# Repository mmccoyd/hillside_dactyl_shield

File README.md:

# Hillside Dactyl Shield

|                 |                 |
|:-----------     |:----------------|
|  |  |

These shields link the parts of a small Dactyl keyboard:
    the MCU, key matrix, battery, USB-C split, display, and underglow.
The shield fits below the index columns and display area of a
    choc Dactyl keyboard.
They should be useful for creating any modest sized Dactyl,
    but were designed for the
    [Hillside Dactyl 50](https://github.com/mmccoyd/hillside_dactyl_50).

## Feature levels

There are three main choice points in a shield cost vs features trade off.
See the wiki ordering page for costs.

- Wireless with key matrix, display, reset, power switch, and battery.
- Wired with ESD protection and PCBA parts placement.
- Vic link, LED underglow, and a decently clean emissions profile,
  using a four layer board with higher setup fees.

## What the shield provides

- A header to socket or solder a ProMicro footprint MCU.
- Key matrix headers for four or five rows, six columns,
   five thumbs, and three external switches.
- A battery switch and JST connector.
- A display header and Vik connector.
- Underglow or side indicator LEDs with power switch and cutoff solder jumpers.
- Extensive ESD protection on the USB-C split connection.
- Four or two layer construction options and PCBA construction.

## Designed as a four layer board, but also to work with two layers

Our highest priority was a cleanly working key matrix,
 followed by an informational display or LED.
Both with clean signal integrity and a properly low
  spurious emissions profile.
So the key matrix routing came first,
  followed by SPI routing for the display and LEDs.
Best practice for SPI seemed to be a four layer board,
    as SPI has fast edge transitions on typical keyboard processors.
Best practice is also to route high speed signals like SPI first,
    but I care more about the key matrix,
    and it seems to have high speed signal edge transitions as well.
So our layout is based on four layers with the inner layers as ground.
That gives the best signal integrity
  and hopefully a properly low emissions profile.
(The signal integrity in the wires flapping around inside the case
    is a different question.)

But four layer boards are more expensive in the small batches
    common with hobbyists.
So a two layer fabrication is also possible,
    as the MCU has direct outer layer ground traces to all ground pin uses.
But with two layers,
  the signal integrity for the matrix, LED, and display is unknown
  and an improper spurious emissions profile seems likely.

## Ordering board fabrication, parts, and building

[Releases](https://github.com/mmccoyd/hillside_dactyl_shield/releases)
    has the files for fabrication.

The [wiki](https://github.com/mmccoyd/hillside_dactyl_shield/wiki)
  has information on parts and ordering.
An example of its use in a keyboard can be found in the
    [Hillside Dactyl 50](https://github.com/mmccoyd/hillside_dactyl_50).

## Firmware

The [Hillside Dactyl 50](https://github.com/mmccoyd/hillside_dactyl_50),
    keyboard's ZMK and QMK firmware
    should be good starting points for creating similar Dactyls.

## Design notes

- The MCU goes face down.
  A dactyl is often not one's first ergo board
  and most ergo boards with a socketed MCU have it face down,
  so most of those building a dactyl likely have MCUs already pinned that way.
- The PCBA is configured for the Vik connector and battery and LED switches.
  It uses KiBot and is being tested using JLC's Economic PCBA.

## Other controller boards

Some other shields provide related abilities, including:

- A board with a built-in processor is
[BastardKB](https://bastardkb.com/)'s [Splinktegrated](https://bastardkb.com/product/splinktegrated-rp2040-controller/)
- The [Keebio Stampy](https://keeb.io/products/stampy-prototypes-rp2040-usb-c-controller-board-for-handwiring)
   RP2040 has three integrated switch footprints plus 26 pin breakouts.

## Images

There is also a STEP file in the GitHub action result files.

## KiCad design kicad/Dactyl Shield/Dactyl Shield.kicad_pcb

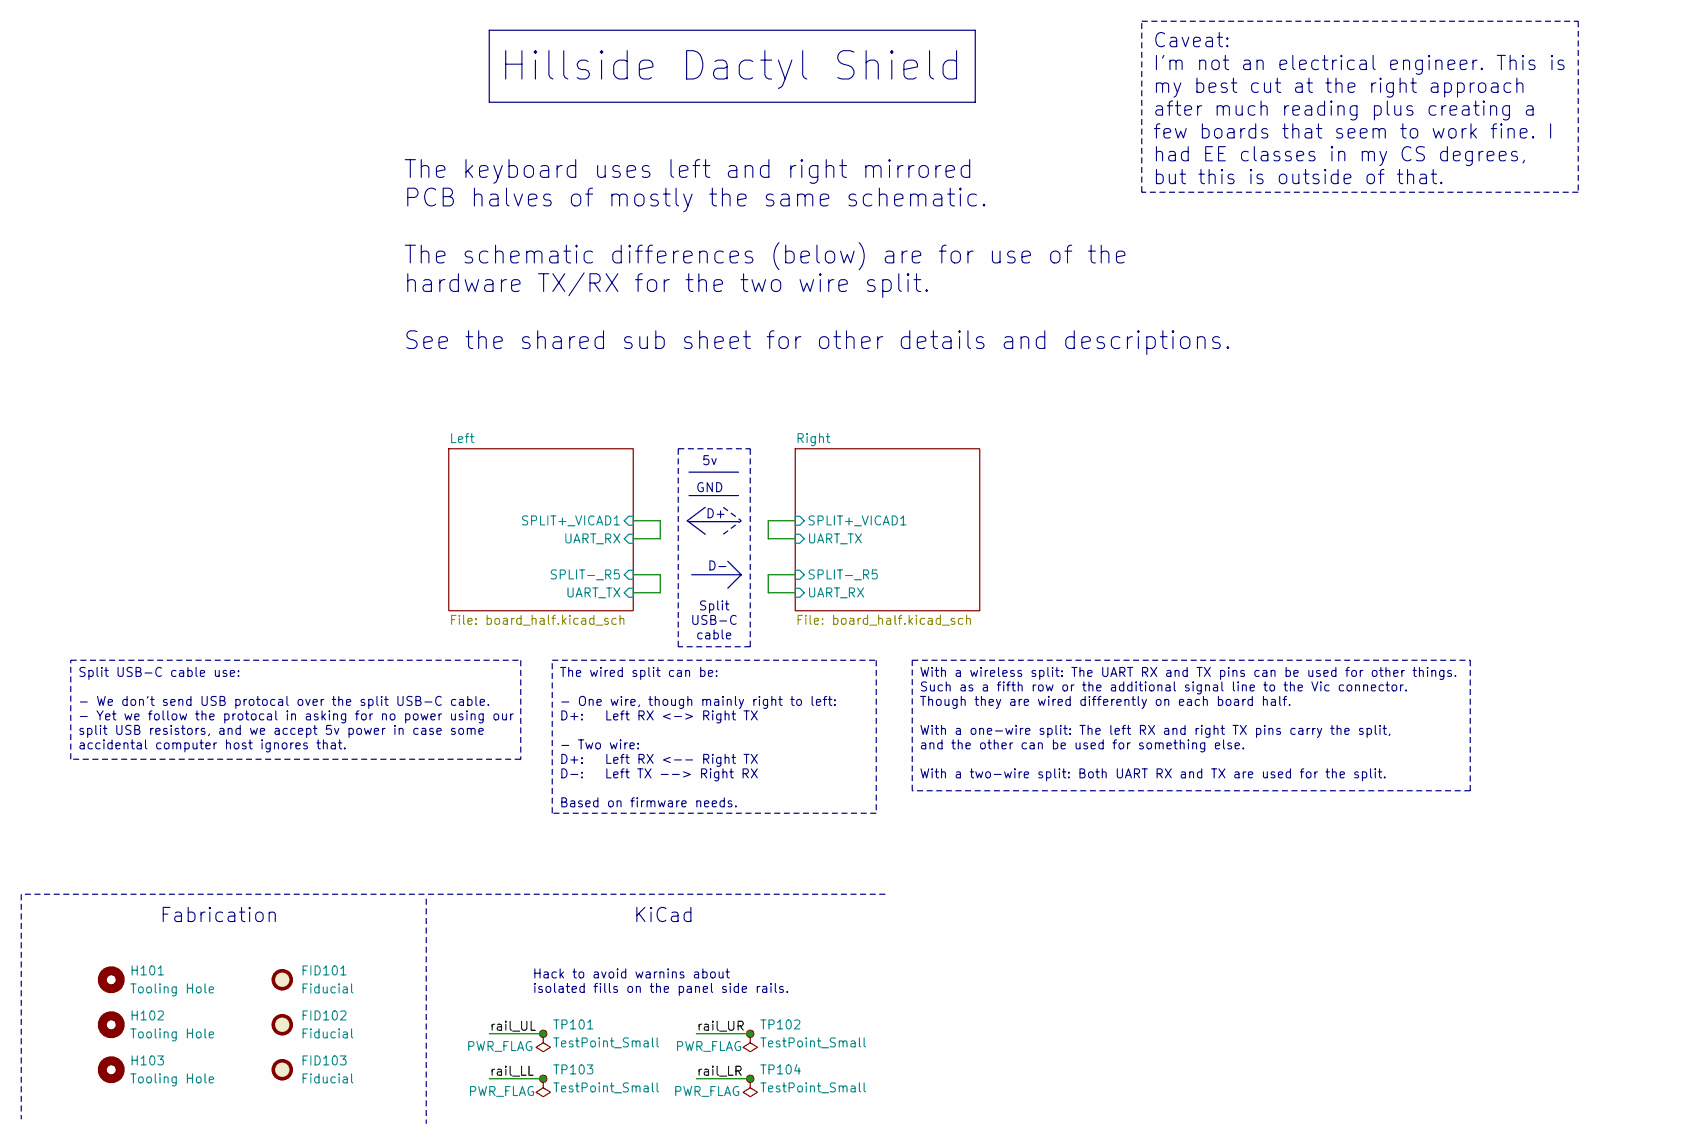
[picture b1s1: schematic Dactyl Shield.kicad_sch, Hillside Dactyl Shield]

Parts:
FID101, FID102, FID103: Fiducial; Fiducial_1mm_Mask2mm
H101, H102, H103: Tooling Hole; ToolingHole_1.152mm
TP101, TP102, TP103, TP104: TestPoint_Small; TestPoint_THTPad_D1.0mm_Drill0.5mm

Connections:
/rail_LL: TP103.1
/rail_LR: TP104.1
/rail_UL: TP101.1
/rail_UR: TP102.1

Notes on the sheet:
KiCad
Fabrication
${TITLE}
GND
The keyboard uses left and right mirrored PCB halves of mostly the same schematic. The schematic differences (below) are for use of the hardware TX/RX for the two wire split. See the shared sub sheet for other details and descriptions.
Hack to avoid warnins about isolated fills on the panel side rails.
Split USB-C cable use: - We don't send USB protocal over the split USB-C cable. - Yet we follow the protocal in asking for no power using our split USB resistors, and we accept 5v power in case some accidental computer host ignores that.
Caveat: I'm not an electrical engineer. This is my best cut at the right approach after much reading plus creating a few boards that seem to work fine. I had EE classes in my CS degrees, but this is outside of that.
With a wireless split: The UART RX and TX pins can be used for other things. Such as a fifth row or the additional signal line to the Vic connector. Though they are wired differently on each board half. With a one-wire split: The left RX and right TX pins carry the split, and the other can be used 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
The wired split can be: - One wire, though mainly right to left: D+: Left RX <-> Right TX - Two wire: D+: Left RX <-- Right TX D-: Left TX --> Right RX Based on firmware needs.
Split USB-C cable

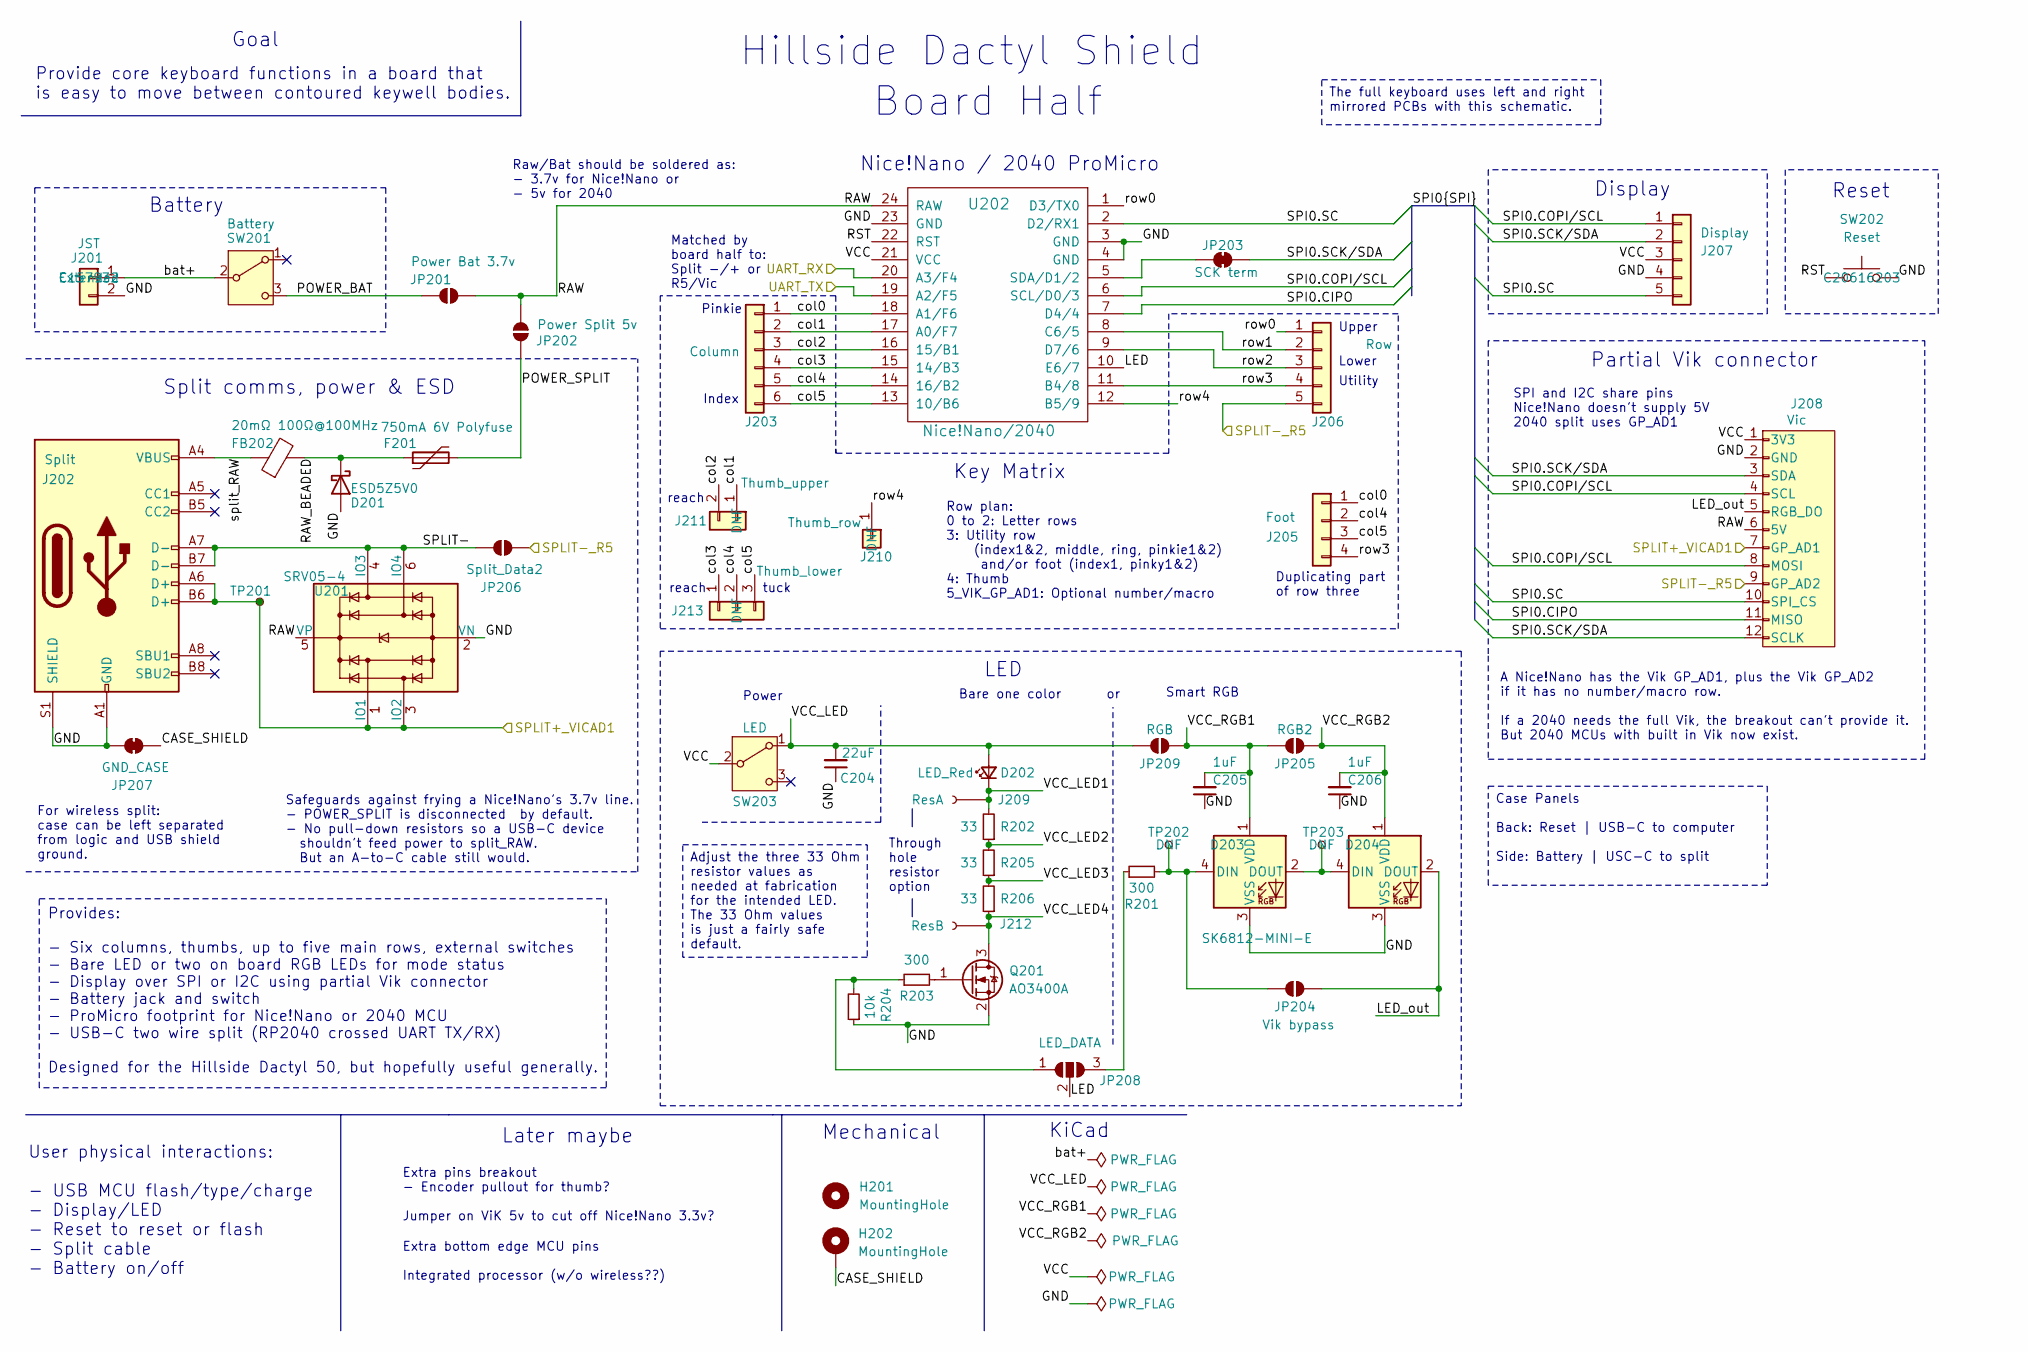
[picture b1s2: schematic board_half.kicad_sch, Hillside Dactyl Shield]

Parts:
C204: 22uF; C_0805_2012Metric; LCSC Part C45783
C205, C206: 1uF; C_0402_1005Metric; LCSC Part C52923
D201: ESD5Z5V0; D_SOD-523; JLC PCBA Type Extended
D202: LED_Red; LED_D5.0mm
D203, D204: SK6812-MINI-E; SK6812-MINI-E-Dog2_1S
F201: 750mA 6V Polyfuse; Fuse_0805_2012Metric; JLC PCBA Type Extended
FB202: 20mΩ 100Ω@100MHz; L_0805_2012Metric; JLC PCBA Type Extended
H201: MountingHole; MountingHole_3.2mm_M3_DIN965
H202: MountingHole; MountingHole_3.2mm_M3_DIN965_Pad
J201: JST; JST_PH_S2B-PH-K_1x02_P2.00mm_Horizontal; JLC PCBA Type Extended
J202: Split; USB_C_Receptacle_HRO_TYPE-C-31-M-12; JLC PCBA Type Extended
J203: Column; PinHeader_Columns
J205: Foot; PinHeader_External
J206: Row; PinHeader_Rows
J207: Display; PinHeader_Display
J208: Vic; vik-keyboard-connector-horizontal; JLC PCBA Type Extended
J209: ResA; Conn_Pin_D0.8mm
J210: Thumb_row; PinHeader_Thumb_row
J211: Thumb_upper; PinHeader_Thumb_upper
J212: ResB; Conn_Pin_D0.8mm
J213: Thumb_lower; PinHeader_Thumb_lower
JP201: Power Bat 3.7v; SolderJumper-2_P1.3mm_Open_RoundedPad1.0x1.5mm
JP202: Power Split 5v; SolderJumper-2_P1.3mm_Open_RoundedPad1.0x1.5mm
JP203: SCK term; SolderJumper-2_P1.3mm_Bridged_RoundedPad1.0x1.5mm
JP204: Vik bypass; SolderJumper-2_P1.3mm_Open_RoundedPad1.0x1.5mm
JP205: RGB2; SolderJumper-2_P1.3mm_Open_RoundedPad1.0x1.5mm
JP206: Split_Data2; SolderJumper-2_P1.3mm_Open_RoundedPad1.0x1.5mm
JP207: GND_CASE; SolderJumper-2_P1.3mm_Bridged_RoundedPad1.0x1.5mm
JP208: LED_DATA; SolderJumper-3_P1.3mm_Open_RoundedPad1.0x1.5mm
JP209: RGB; SolderJumper-2_P1.3mm_Open_RoundedPad1.0x1.5mm
Q201: AO3400A; SOT-23; JLC PCBA Type Econom
R201, R203: 300; R_0603_1608Metric; LCSC Part C23025
R202, R205, R206: 33; R_0805_2012Metric_Pad1.20x1.40mm_HandSolder; LCSC Part C17634
R204: 10k; R_0603_1608Metric; LCSC Part C25804
SW201: Battery; SW_SPDT_Battery; JLC PCBA Type Standard
SW202: Reset; SW_Tactile_SKHL_Angled; LCSC Part C20616203
SW203: LED; SW_SPDT_JS202011AQN_wider; JLC PCBA Type Standard
TP201, TP202, TP203: TestPoint_Small; TestPoint_THTPad_D1.0mm_Drill0.5mm
U201: SRV05-4; SOT-23-6; JLC PCBA Type Extended Prefer
U202: Nice!Nano/2040; ProMicro_v2_1S

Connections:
/Right/CASE_SHIELD: H202.1, JP207.2 (B)
/Right/GND: C204.1, C205.1, C206.1, D201.2 (A), D203.3 (VSS), D204.3 (VSS), J201.2, J202.A1 (GND), J202.A12 (GND), J202.B1 (GND), J202.B12 (GND), J202.S1 (SHIELD), J207.4, J208.2 (GND), JP207.1 (A), Q201.2 (S), R204.1, SW202.1, U201.2 (VN), U202.3 (GND), U202.4 (GND), U202.23 (GND)
/Right/LED: JP208.2 (C), U202.10 (E6/7)
/Right/LED_out: D204.2 (DOUT), J208.5 (RGB_DO), JP204.2 (B)
/Right/POWER_BAT: JP201.1 (A), SW201.3 (C)
/Right/POWER_SPLIT: F201.2, JP202.1 (A)
/Right/RAW: J208.6 (5V), JP201.2 (B), JP202.2 (B), U201.5 (VP), U202.24 (RAW)
/Right/RAW_BEADED: D201.1 (K), F201.1, FB202.2
/Right/RST: SW202.2, U202.22 (RST)
/Right/SPI0.CIPO: J208.11 (MISO), U202.7 (D4/4)
/Right/SPI0.COPI/SCL: J207.1, J208.4 (SCL), J208.8 (MOSI), U202.6 (SCL/D0/3)
/Right/SPI0.SC: J207.5, J208.10 (SPI_CS), U202.2 (D2/RX1)
/Right/SPI0.SCK/SDA: J207.2, J208.3 (SDA), J208.12 (SCLK), JP203.2 (B)
/Right/SPLIT+_VICAD1: J202.A6 (D+), J202.B6 (D+), J208.7 (GP_AD1), TP201.1, U201.1 (IO1), U201.3 (IO2), U202.19 (A2/F5)
/Right/SPLIT-: J202.A7 (D-), J202.B7 (D-), JP206.1 (A), U201.4 (IO3), U201.6 (IO4)
/Right/SPLIT-_R5: J206.5, J208.9 (GP_AD2), JP206.2 (B), U202.20 (A3/F4)
/Right/VCC: J207.3, J208.1 (3V3), SW203.2 (B), U202.21 (VCC)
/Right/VCC_LED: C204.2, D202.2 (A), JP209.1 (A), SW203.1 (A)
/Right/VCC_LED1: D202.1 (K), J209.1, R202.2
/Right/VCC_LED2: R202.1, R205.2
/Right/VCC_LED3: R205.1, R206.2
/Right/VCC_LED4: J212.1, Q201.3 (D), R206.1
/Right/VCC_RGB1: C205.2, D203.1 (VDD), JP205.1 (A), JP209.2 (B)
/Right/VCC_RGB2: C206.2, D204.1 (VDD), JP205.2 (B)
/Right/bat+: J201.1, SW201.2 (B)
/Right/col0: J203.1, J205.1, U202.18 (A1/F6)
/Right/col1: J203.2, J211.1, U202.17 (A0/F7)
/Right/col2: J203.3, J211.2, U202.16 (15/B1)
/Right/col3: J203.4, J213.1, U202.15 (14/B3)
/Right/col4: J203.5, J205.2, J213.2, U202.14 (16/B2)
/Right/col5: J203.6, J205.3, J213.3, U202.13 (10/B6)
/Right/row0: J206.1, U202.1 (D3/TX0)
/Right/row1: J206.2, U202.8 (C6/5)
/Right/row2: J206.3, U202.9 (D7/6)
/Right/row3: J205.4, J206.4, U202.11 (B4/8)
/Right/row4: J210.1, U202.12 (B5/9)
/Right/split_RAW: FB202.1, J202.A4 (VBUS), J202.A9 (VBUS), J202.B4 (VBUS), J202.B9 (VBUS)
unnamed: D203.4 (DIN), JP204.1 (A), R201.2, TP202.1
unnamed: D203.2 (DOUT), D204.4 (DIN), TP203.1
unnamed: JP203.1 (A), U202.5 (SDA/D1/2)
unnamed: JP208.1 (A), R203.1, R204.2
unnamed: JP208.3 (B), R201.1
unnamed: Q201.1 (G), R203.2

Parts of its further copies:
C304: 22uF; C_0805_2012Metric; LCSC Part C45783
C305, C306: 1uF; C_0402_1005Metric; LCSC Part C52923
D301: ESD5Z5V0; D_SOD-523; JLC PCBA Type Extended
D302: LED_Red; LED_D5.0mm
D303, D304: SK6812-MINI-E; SK6812-MINI-E-Dog2_1S
F301: 750mA 6V Polyfuse; Fuse_0805_2012Metric; JLC PCBA Type Extended
FB302: 20mΩ 100Ω@100MHz; L_0805_2012Metric; JLC PCBA Type Extended
H301: MountingHole; MountingHole_3.2mm_M3_DIN965
H302: MountingHole; MountingHole_3.2mm_M3_DIN965_Pad
J301: JST; JST_PH_S2B-PH-K_1x02_P2.00mm_Horizontal; JLC PCBA Type Extended
J302: Split; USB_C_Receptacle_HRO_TYPE-C-31-M-12; JLC PCBA Type Extended
J303: Column; PinHeader_Columns
J305: Foot; PinHeader_External
J306: Row; PinHeader_Rows
J307: Display; PinHeader_Display
J308: Vic; vik-keyboard-connector-horizontal; JLC PCBA Type Extended
J309: ResA; Conn_Pin_D0.8mm
J310: Thumb_row; PinHeader_Thumb_row
J311: Thumb_upper; PinHeader_Thumb_upper
J312: ResB; Conn_Pin_D0.8mm
J313: Thumb_lower; PinHeader_Thumb_lower
JP301: Power Bat 3.7v; SolderJumper-2_P1.3mm_Open_RoundedPad1.0x1.5mm
JP302: Power Split 5v; SolderJumper-2_P1.3mm_Open_RoundedPad1.0x1.5mm
JP303: SCK term; SolderJumper-2_P1.3mm_Bridged_RoundedPad1.0x1.5mm
JP304: Vik bypass; SolderJumper-2_P1.3mm_Open_RoundedPad1.0x1.5mm
JP305: RGB2; SolderJumper-2_P1.3mm_Open_RoundedPad1.0x1.5mm
JP306: Split_Data2; SolderJumper-2_P1.3mm_Open_RoundedPad1.0x1.5mm
JP307: GND_CASE; SolderJumper-2_P1.3mm_Bridged_RoundedPad1.0x1.5mm
JP309: RGB; SolderJumper-2_P1.3mm_Open_RoundedPad1.0x1.5mm
JP310: LED_DATA; SolderJumper-3_P1.3mm_Open_RoundedPad1.0x1.5mm
Q301: AO3400A; SOT-23; JLC PCBA Type Econom
R301, R303: 300; R_0603_1608Metric; LCSC Part C23025
R302, R305, R306: 33; R_0805_2012Metric_Pad1.20x1.40mm_HandSolder; LCSC Part C17634
R304: 10k; R_0603_1608Metric; LCSC Part C25804
SW301: Battery; SW_SPDT_Battery; JLC PCBA Type Standard
SW302: Reset; SW_Tactile_SKHL_Angled; LCSC Part C20616203
SW303: LED; SW_SPDT_JS202011AQN_wider; JLC PCBA Type Standard
TP301, TP302, TP303: TestPoint_Small; TestPoint_THTPad_D1.0mm_Drill0.5mm
U301: SRV05-4; SOT-23-6; JLC PCBA Type Extended Prefer
U302: Nice!Nano/2040; ProMicro_v2_1S

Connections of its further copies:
/Left/CASE_SHIELD: H302.1, JP307.2 (B)
/Left/GND: C304.1, C305.1, C306.1, D301.2 (A), D303.3 (VSS), D304.3 (VSS), J301.2, J302.A1 (GND), J302.A12 (GND), J302.B1 (GND), J302.B12 (GND), J302.S1 (SHIELD), J307.4, J308.2 (GND), JP307.1 (A), Q301.2 (S), R304.1, SW302.1, U301.2 (VN), U302.3 (GND), U302.4 (GND), U302.23 (GND)
/Left/LED: JP310.2 (C), U302.10 (E6/7)
/Left/LED_out: D304.2 (DOUT), J308.5 (RGB_DO), JP304.2 (B)
/Left/POWER_BAT: JP301.1 (A), SW301.3 (C)
/Left/POWER_SPLIT: F301.2, JP302.1 (A)
/Left/RAW: J308.6 (5V), JP301.2 (B), JP302.2 (B), U301.5 (VP), U302.24 (RAW)
/Left/RAW_BEADED: D301.1 (K), F301.1, FB302.2
/Left/RST: SW302.2, U302.22 (RST)
/Left/SPI0.CIPO: J308.11 (MISO), U302.7 (D4/4)
/Left/SPI0.COPI/SCL: J307.1, J308.4 (SCL), J308.8 (MOSI), U302.6 (SCL/D0/3)
/Left/SPI0.SC: J307.5, J308.10 (SPI_CS), U302.2 (D2/RX1)
/Left/SPI0.SCK/SDA: J307.2, J308.3 (SDA), J308.12 (SCLK), JP303.2 (B)
/Left/SPLIT+_VICAD1: J302.A6 (D+), J302.B6 (D+), J308.7 (GP_AD1), TP301.1, U301.1 (IO1), U301.3 (IO2), U302.20 (A3/F4)
/Left/SPLIT-: J302.A7 (D-), J302.B7 (D-), JP306.1 (A), U301.4 (IO3), U301.6 (IO4)
/Left/SPLIT-_R5: J306.5, J308.9 (GP_AD2), JP306.2 (B), U302.19 (A2/F5)
/Left/VCC: J307.3, J308.1 (3V3), SW303.2 (B), U302.21 (VCC)
/Left/VCC_LED: C304.2, D302.2 (A), JP309.1 (A), SW303.1 (A)
/Left/VCC_LED1: D302.1 (K), J309.1, R302.2
/Left/VCC_LED2: R302.1, R305.2
/Left/VCC_LED3: R305.1, R306.2
/Left/VCC_LED4: J312.1, Q301.3 (D), R306.1
/Left/VCC_RGB1: C305.2, D303.1 (VDD), JP305.1 (A), JP309.2 (B)
/Left/VCC_RGB2: C306.2, D304.1 (VDD), JP305.2 (B)
/Left/bat+: J301.1, SW301.2 (B)
/Left/col0: J303.1, J305.1, U302.18 (A1/F6)
/Left/col1: J303.2, J311.1, U302.17 (A0/F7)
/Left/col2: J303.3, J311.2, U302.16 (15/B1)
/Left/col3: J303.4, J313.1, U302.15 (14/B3)
/Left/col4: J303.5, J305.2, J313.2, U302.14 (16/B2)
/Left/col5: J303.6, J305.3, J313.3, U302.13 (10/B6)
/Left/row0: J306.1, U302.1 (D3/TX0)
/Left/row1: J306.2, U302.8 (C6/5)
/Left/row2: J306.3, U302.9 (D7/6)
/Left/row3: J305.4, J306.4, U302.11 (B4/8)
/Left/row4: J310.1, U302.12 (B5/9)
/Left/split_RAW: FB302.1, J302.A4 (VBUS), J302.A9 (VBUS), J302.B4 (VBUS), J302.B9 (VBUS)
unnamed: D303.4 (DIN), JP304.1 (A), R301.2, TP302.1
unnamed: D303.2 (DOUT), D304.4 (DIN), TP303.1
unnamed: JP303.1 (A), U302.5 (SDA/D1/2)
unnamed: JP310.1 (A), R303.1, R304.2
unnamed: JP310.3 (B), R301.1
unnamed: Q301.1 (G), R303.2

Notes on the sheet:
Extra pins breakout - Encoder pullout for thumb? Jumper on ViK 5v to cut off Nice!Nano 3.3v?
SPI and I2C share pins Nice!Nano doesn't supply 5V 2040 split uses GP_AD1
Duplicating part of row three
Matched by board half to: Split -/+ or R5/Vic
Upper
Board Half
Index
For wireless split: case can be left separated from logic and USB shield ground.
Through hole resistor option
Utility
Battery
Key Matrix
Bare one color
tuck
Pinkie
Row plan: 0 to 2: Letter rows 3: Utility row (index1&2, middle, ring, pinkie1&2) and/or foot (index1, pinky1&2) 4: Thumb 5_VIK_GP_AD1: Optional number/macro
Safeguards against frying a Nice!Nano's 3.7v line. - POWER_SPLIT is disconnected by default. - No pull-down resistors so a USB-C device shouldn't feed power to split_RAW. But an A-to-C cable still would.
Smart RGB
Lower
Display
KiCad
${TITLE}
Provide core keyboard functions in a board that is easy to move between contoured keywell bodies.
User physical interactions: - USB MCU flash/type/charge - Display/LED - Reset to reset or flash - Split cable - Battery on/off
reach
Goal
Mechanical
Nice!Nano / 2040 ProMicro
Power
Partial Vik connector
LED
Raw/Bat should be soldered as: - 3.7v for Nice!Nano or - 5v for 2040
Later maybe
Reset
Extra bottom edge MCU pins Integrated processor (w/o wireless??)
A Nice!Nano has the Vik GP_AD1, plus the Vik GP_AD2 if it has no number/macro row. If a 2040 needs the full Vik, the breakout can't provide it. But 2040 MCUs with built in Vik now exist.
The full keyboard uses left and right mirrored PCBs with this schematic.
Adjust the three 33 Ohm resistor values as needed at fabrication for the intended LED. The 33 Ohm values is just a fairly safe default.
Provides: - Six columns, thumbs, up to five main rows, external switches - Bare LED or two on board RGB LEDs for mode status - Display over SPI or I2C using partial Vik connector - Battery jack and switch - ProMicro footprint for Nice!Nano or 2040 MCU - USB-C two wire split (RP2040 crossed UART TX/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
Case Panels Back: Reset | USB-C to computer Side: Battery | USC-C to split

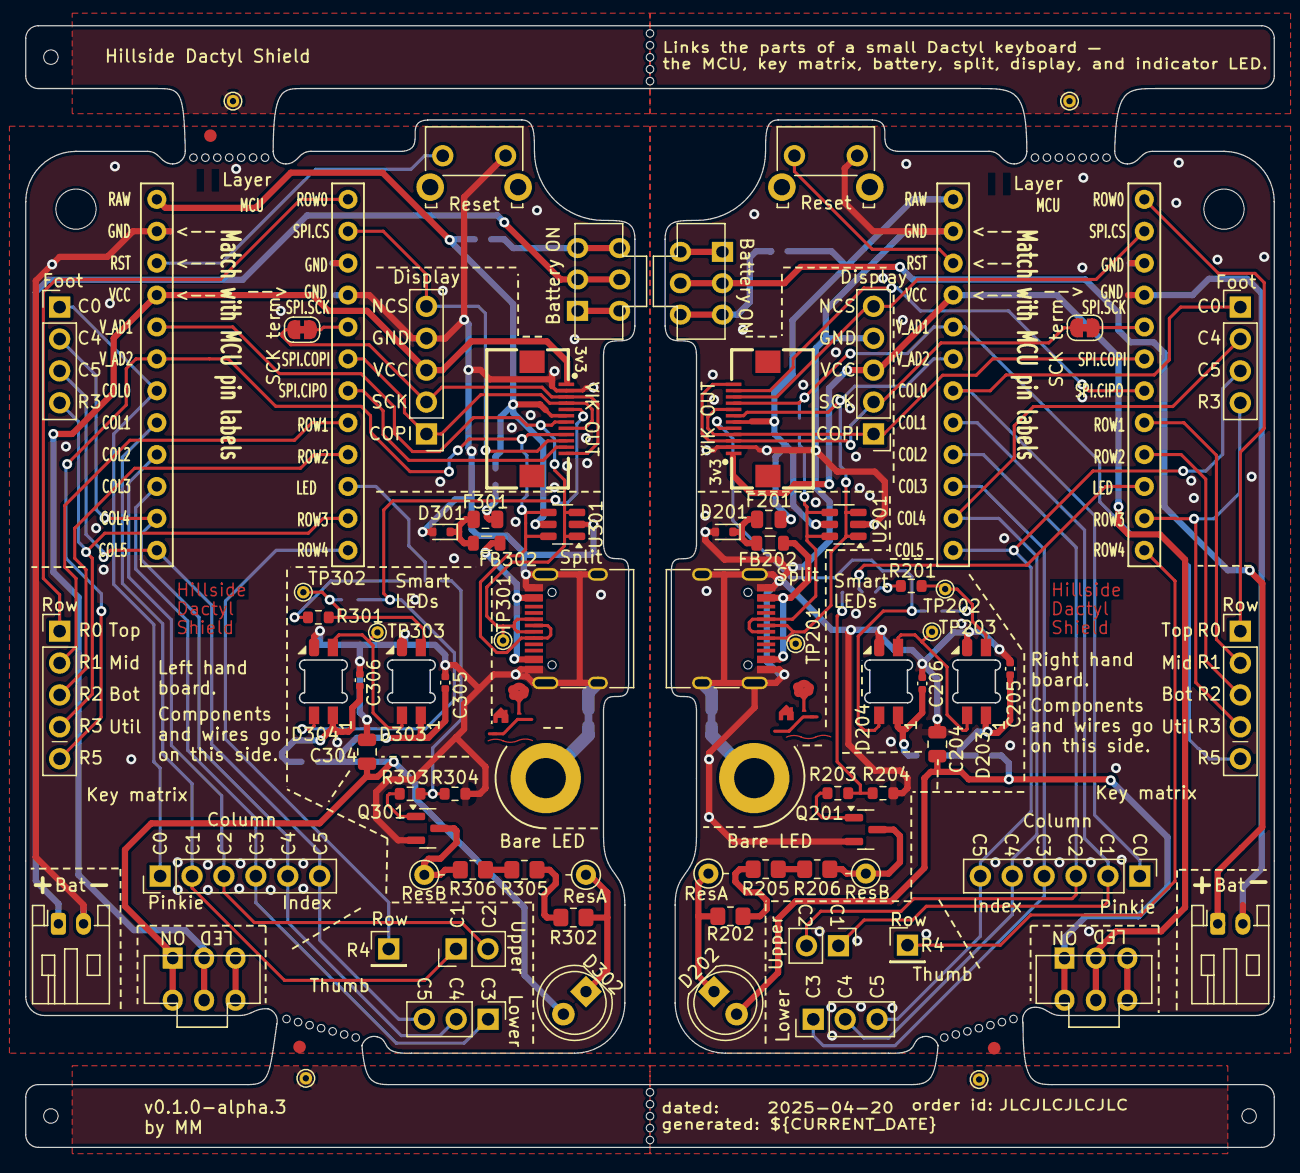
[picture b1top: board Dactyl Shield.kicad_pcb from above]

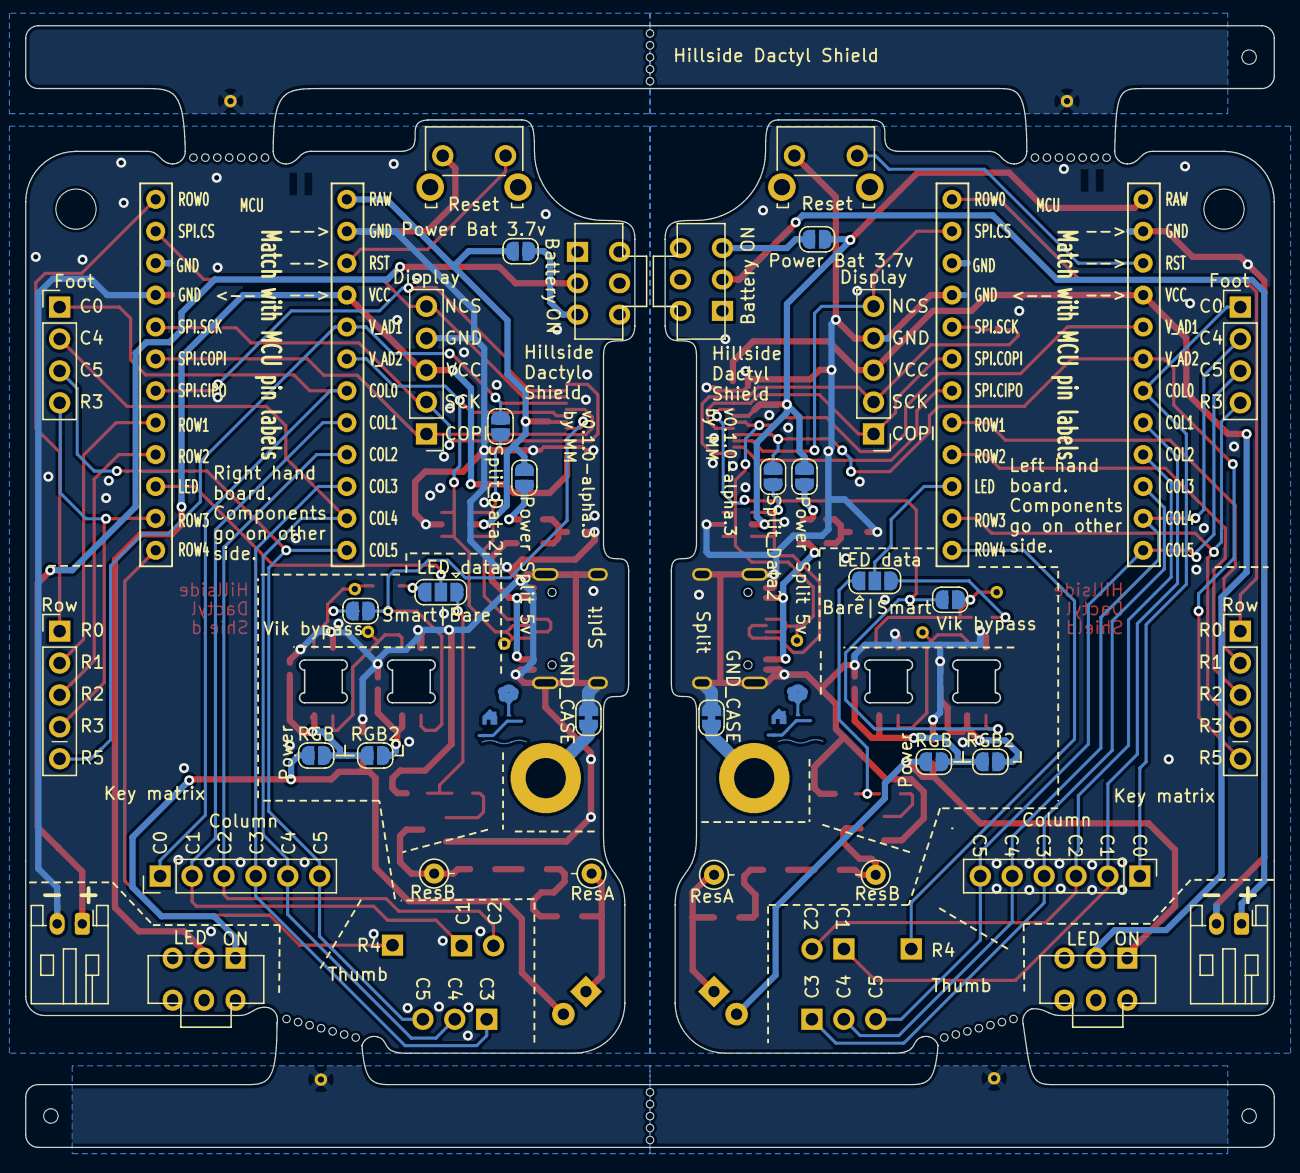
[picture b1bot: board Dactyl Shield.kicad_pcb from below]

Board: 4 copper layers, 99.4 x 89.3 mm, 104 parts (16 on the bottom side), 86 nets.

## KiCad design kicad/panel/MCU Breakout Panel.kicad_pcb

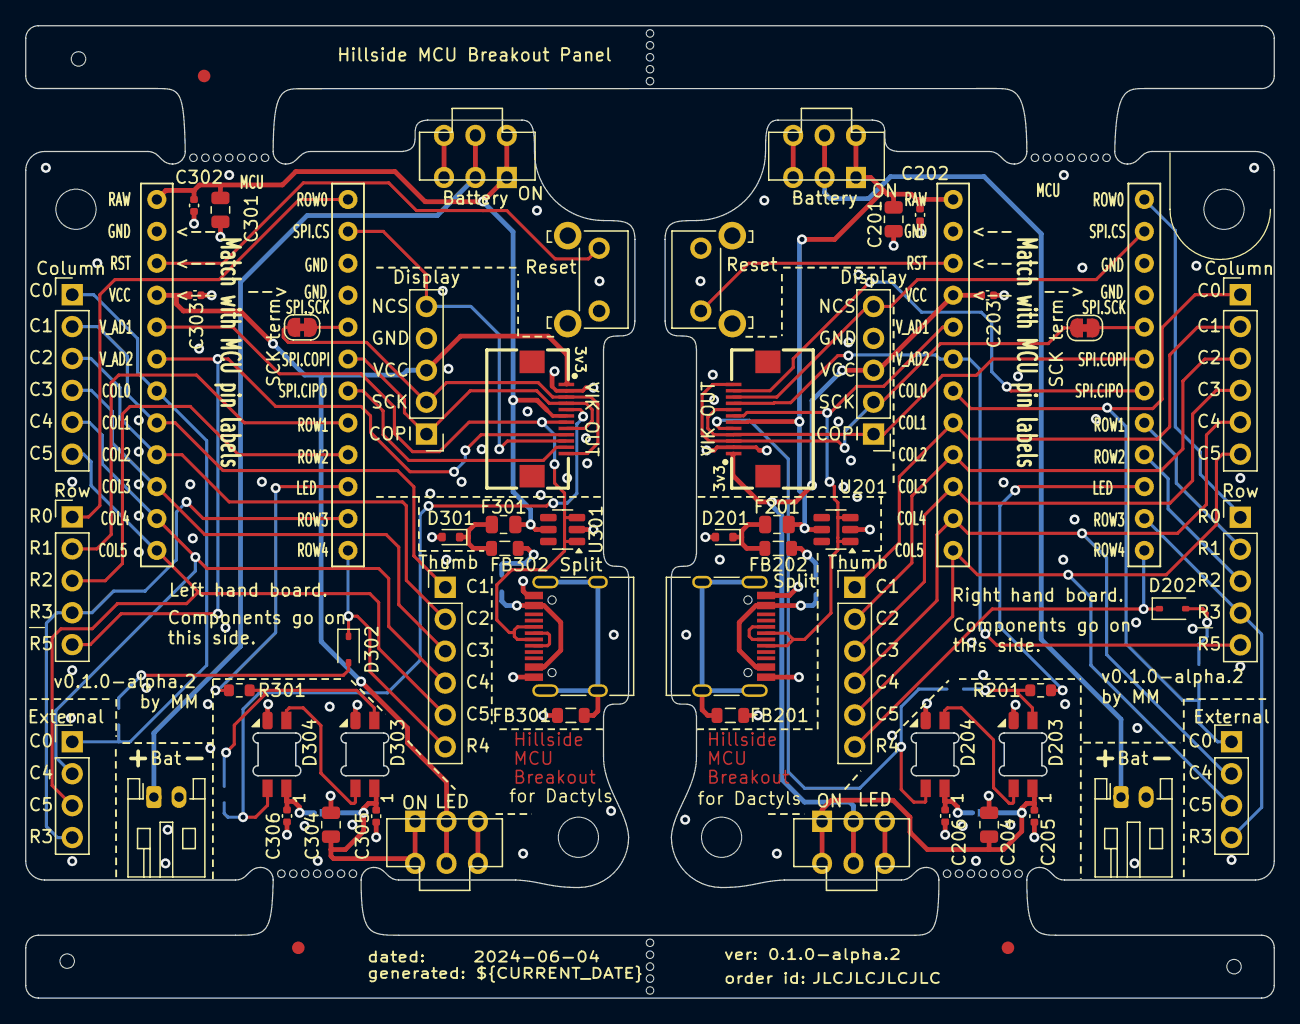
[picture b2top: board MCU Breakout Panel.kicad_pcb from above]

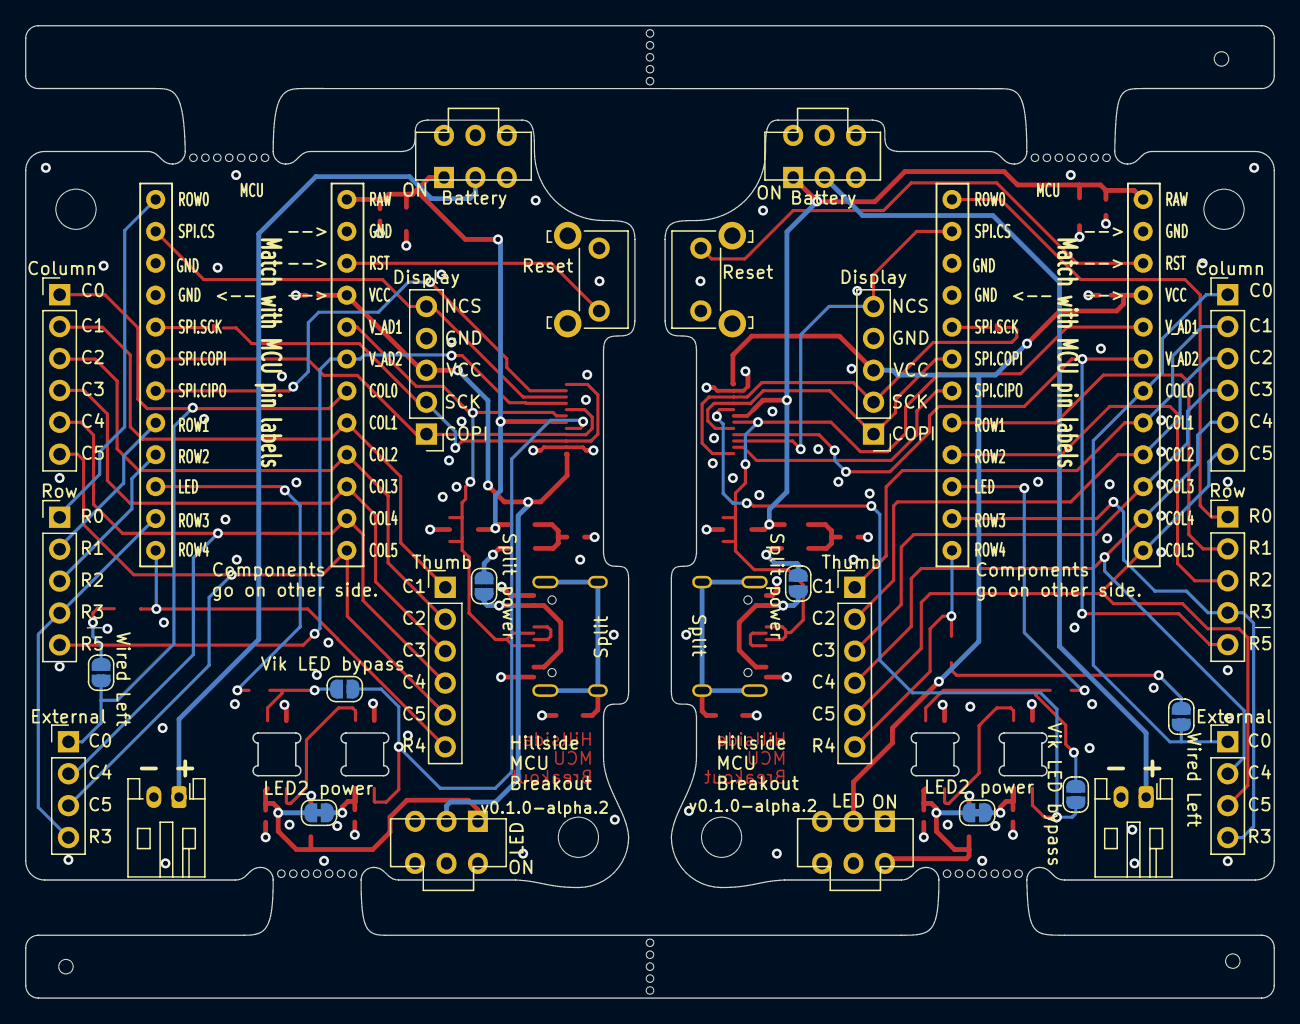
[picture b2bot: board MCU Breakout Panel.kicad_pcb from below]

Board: 4 copper layers, 99.4 x 77.4 mm, 74 parts (8 on the bottom side), 70 nets.

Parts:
C201, C301: 4.7uF; C_0805_2012Metric
C202, C203, C205, C206, C302, C303, C305, C306: 0.1uF; C_0402_1005Metric
C204, C304: 22uF; C_0805_2012Metric
D201, D301: ESD5Z5V0; D_SOD-523
D202, D302: D_Small; D_SOD-323
D203, D204, D303, D304: SK6812-MINI-E; SK6812-MINI-E-Dog2_1S
F201, F301: 750mA 6V Polyfuse; Fuse_0805_2012Metric
FB201, FB202, FB301, FB302: 20mΩ 100Ω@100MHz; L_0805_2012Metric
FID1, FID2, FID3: Fiducial; Fiducial_1mm_Mask2mm
H3, H4, H5: ToolingHole; ToolingHole_1.152mm
H201, H202, H301, H302: MountingHole; MountingHole_3.2mm_M3_DIN965
J201, J301: JST; JST_PH_S2B-PH-K_1x02_P2.00mm_Horizontal
J202, J302: Split; USB_C_Receptacle_HRO_TYPE-C-31-M-12
J203, J303: Column; PinHeader_Columns
J204, J304: Thumb; PinHeader_Thumbs
J205, J305: External; PinHeader_External
J206, J306: Row; PinHeader_Rows
J207, J307: Display; PinHeader_Display
J208, J308: Vic; vik-keyboard-connector-horizontal
JP201, JP301: Split power; SolderJumper-2_P1.3mm_Open_RoundedPad1.0x1.5mm
JP202, JP302: Wired Left; SolderJumper-2_P1.3mm_Open_RoundedPad1.0x1.5mm
JP203, JP303: SCK term; SolderJumper-2_P1.3mm_Bridged_RoundedPad1.0x1.5mm
JP204, JP304: Vik LED bypass; SolderJumper-2_P1.3mm_Open_RoundedPad1.0x1.5mm
JP205, JP305: LED2 power; SolderJumper-2_P1.3mm_Bridged_RoundedPad1.0x1.5mm
R201, R301: 300 Ohm; R_0603_1608Metric
SW201, SW301: Battery; SW_SPDT_Battery
SW202, SW302: Reset; SW_Tactile_SKHL_Angled
SW203, SW303: LED; SW_SPDT_JS202011AQN_wider
U201, U301: SRV05-4; SOT-23-6
U202, U302: Nice!Nano/2040; ProMicro_v2_1S

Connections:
/Left/GND: C301.1, C302.1, C303.1, C304.1, C305.1, C306.1, D301.2 (A), D303.3 (VSS), D304.3 (VSS), FB301.2, J301.2, J302.A1 (GND), J302.A12 (GND), J302.B1 (GND), J302.B12 (GND), J307.4, J308.2 (GND), SW302.1, U301.2 (VN), U302.3 (GND), U302.4 (GND), U302.23 (GND)
/Left/LED: R301.1, U302.10 (E6/7)
/Left/LED_out: D304.2 (DOUT), J308.5 (RGB_DO), JP304.2 (B)
/Left/RAW: C301.2, C302.2, F301.2, J308.6 (5V), SW301.1 (A), U301.5 (VP), U302.24 (RAW)
/Left/RAW_BEADED: D301.1 (K), F301.1, FB302.2
/Left/RAW_ENABLED: FB302.1, JP301.2 (B)
/Left/RST: SW302.2, U302.22 (RST)
/Left/SHIELD: FB301.1, J302.S1 (SHIELD)
/Left/SPI0.CIPO: J308.11 (MISO), U302.7 (D4/4)
/Left/SPI0.COPI/SCL: J307.1, J308.4 (SCL), J308.8 (MOSI), U302.6 (SCL/D0/3)
/Left/SPI0.SC: J307.5, J308.10 (SPI_CS), U302.2 (D2/RX1)
/Left/SPI0.SCK/SDA: J307.2, J308.3 (SDA), J308.12 (SCLK), JP303.2 (B)
/Left/SPLIT_VIK_GP_AD1: J302.A6 (D+), J302.B6 (D+), J308.7 (GP_AD1), U301.1 (IO1), U301.3 (IO2), U302.20 (A3/F4)
/Left/VCC: C303.2, J307.3, J308.1 (3V3), SW303.2 (B), U302.21 (VCC)
/Left/VCC_LED1: C304.2, C305.2, D303.1 (VDD), JP305.1 (A), SW303.1 (A)
/Left/VCC_LED2: C306.2, D304.1 (VDD), JP305.2 (B)
/Left/bat+: J301.1, SW301.2 (B)
/Left/col0: J303.1, J305.1, JP302.1 (A), U302.18 (A1/F6)
/Left/col1: J303.2, J304.1, U302.17 (A0/F7)
/Left/col2: J303.3, J304.2, U302.16 (15/B1)
/Left/col3: J303.4, J304.3, U302.15 (14/B3)
/Left/col4: J303.5, J304.4, J305.2, U302.14 (16/B2)
/Left/col5: J303.6, J304.5, J305.3, U302.13 (10/B6)
/Left/row0: J306.1, U302.1 (D3/TX0)
/Left/row1: J306.2, U302.8 (C6/5)
/Left/row2: J306.3, U302.9 (D7/6)
/Left/row3: J305.4, J306.4, U302.11 (B4/8)
/Left/row4: D302.1 (K), J304.6, U302.12 (B5/9)
/Left/row5_VIK_GP_AD2: J306.5, J308.9 (GP_AD2), U302.19 (A2/F5)
/Left/split_RAW: J302.A4 (VBUS), J302.A9 (VBUS), J302.B4 (VBUS), J302.B9 (VBUS), JP301.1 (A)
/Right/GND: C201.1, C202.1, C203.1, C204.1, C205.1, C206.1, D201.2 (A), D203.3 (VSS), D204.3 (VSS), FB201.2, J201.2, J202.A1 (GND), J202.A12 (GND), J202.B1 (GND), J202.B12 (GND), J207.4, J208.2 (GND), SW202.1, U201.2 (VN), U202.3 (GND), U202.4 (GND), U202.23 (GND)
/Right/LED: R201.1, U202.10 (E6/7)
/Right/LED_out: D204.2 (DOUT), J208.5 (RGB_DO), JP204.2 (B)
/Right/RAW: C201.2, C202.2, F201.2, J208.6 (5V), SW201.1 (A), U201.5 (VP), U202.24 (RAW)
/Right/RAW_BEADED: D201.1 (K), F201.1, FB202.2
/Right/RAW_ENABLED: FB202.1, JP201.2 (B)
/Right/RST: SW202.2, U202.22 (RST)
/Right/SHIELD: FB201.1, J202.S1 (SHIELD)
/Right/SPI0.CIPO: J208.11 (MISO), U202.7 (D4/4)
/Right/SPI0.COPI/SCL: J207.1, J208.4 (SCL), J208.8 (MOSI), U202.6 (SCL/D0/3)
/Right/SPI0.SC: J207.5, J208.10 (SPI_CS), U202.2 (D2/RX1)
/Right/SPI0.SCK/SDA: J207.2, J208.3 (SDA), J208.12 (SCLK), JP203.2 (B)
/Right/SPLIT_VIK_GP_AD1: J202.A6 (D+), J202.B6 (D+), J208.7 (GP_AD1), U201.1 (IO1), U201.3 (IO2), U202.20 (A3/F4)
/Right/VCC: C203.2, J207.3, J208.1 (3V3), SW203.2 (B), U202.21 (VCC)
/Right/VCC_LED1: C204.2, C205.2, D203.1 (VDD), JP205.1 (A), SW203.1 (A)
/Right/VCC_LED2: C206.2, D204.1 (VDD), JP205.2 (B)
/Right/bat+: J201.1, SW201.2 (B)
/Right/col0: J203.1, J205.1, JP202.1 (A), U202.18 (A1/F6)
/Right/col1: J203.2, J204.1, U202.17 (A0/F7)
/Right/col2: J203.3, J204.2, U202.16 (15/B1)
/Right/col3: J203.4, J204.3, U202.15 (14/B3)
/Right/col4: J203.5, J204.4, J205.2, U202.14 (16/B2)
/Right/col5: J203.6, J204.5, J205.3, U202.13 (10/B6)
/Right/row0: J206.1, U202.1 (D3/TX0)
/Right/row1: J206.2, U202.8 (C6/5)
/Right/row2: J206.3, U202.9 (D7/6)
/Right/row3: J205.4, J206.4, U202.11 (B4/8)
/Right/row4: D202.1 (K), J204.6, U202.12 (B5/9)
/Right/row5_VIK_GP_AD2: J206.5, J208.9 (GP_AD2), U202.19 (A2/F5)
/Right/split_RAW: J202.A4 (VBUS), J202.A9 (VBUS), J202.B4 (VBUS), J202.B9 (VBUS), JP201.1 (A)
unnamed: D202.2 (A), JP202.2 (B)
unnamed: D203.4 (DIN), JP204.1 (A), R201.2
unnamed: D203.2 (DOUT), D204.4 (DIN)
unnamed: D302.2 (A), JP302.2 (B)
unnamed: D303.4 (DIN), JP304.1 (A), R301.2
unnamed: D303.2 (DOUT), D304.4 (DIN)
unnamed: J202.A7 (D-), J202.B7 (D-)
unnamed: J302.A7 (D-), J302.B7 (D-)
unnamed: JP203.1 (A), U202.5 (SDA/D1/2)
unnamed: JP303.1 (A), U302.5 (SDA/D1/2)
